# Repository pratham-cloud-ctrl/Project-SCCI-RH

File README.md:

# Project SCCI RH

### A spinal interface concept, from scientific question to inspectable engineering

An entirely digital research and engineering project exploring **invasive spinal
cord–computer interfaces (SCCI)**: record relevant activity, interpret it,
select an individualized intervention, and observe the response.

**Two ambitions:** expert-informed practice that could improve retained motor
learning, and feedback over a selected physiological function.

**[Inspect the build in your browser](https://pratham-cloud-ctrl.github.io/Project-SCCI-RH/)** ·
[Explore the project](docs/explore/README.md) ·
[Read the paper](output/pdf/Project_SCCI_RH_Integrated_Manuscript.pdf) ·
[Download the engineering release](https://github.com/pratham-cloud-ctrl/Project-SCCI-RH/releases/tag/v2.1.1)

**No CAD software needed to inspect:** the browser inspector provides selectable
3D assemblies, all eight populated boards, interactive component/net lookup,
all four copper layers and 80 searchable schematic sheets. The
[download panel](https://pratham-cloud-ctrl.github.io/Project-SCCI-RH/?view=downloads)
also supplies standard **STEP solids**, complete **FreeCAD** files and complete
**KiCad** projects for local inspection and editing.

| Future implanted-interface concept | Full-scale engineering reference |
|:---:|:---:|
|  |  |
| **60 × 58 × 14 mm**, before leads. A proposed miniaturized package. | **600 × 310 × 240 mm**, including feet. Actual board geometry at 1:1 scale. |

## Choose what you want to explore

| | Open the guide | What you can inspect |
|---|---|---|
| **01 · Theory & mechanisms** | [Understand the idea](docs/explore/theory.md) | Both application mechanisms, the assumptions behind them, evidence and mathematical models |
| **02 · CAD & 3D models** | [Explore the mechanical design](docs/explore/cad.md) | Assembled/exploded views, rotatable meshes, editable FreeCAD files, STEP exports and drawings |
| **03 · Electronics & KiCad** | [Browse the eight boards](docs/explore/electronics.md) | Board gallery, circuit roles, schematic PDF, native projects, layouts and component lists |
| **04 · Firmware & software** | [Follow the implemented logic](docs/explore/firmware.md) | Current nRF5340 image, production control code, packet handling and runnable verification |
| **05 · Evidence & reproduction** | [Review the work](docs/explore/reviewer-guide.md) | A short reviewer walkthrough, results, requirements, source records and reproduction commands |

Use the browser inspector for viewing. Links labelled **native source** lead to
engineering files that GitHub may offer only as downloads. Use the complete
packages in the inspector to open them locally; the guides explain the required
software, dependencies and how to preserve the released originals.

## The project in one loop

**Observe → interpret → calibrate → request stimulation → supervise delivery → observe response.**

For motor learning, expert performance informs a task-conditioned reference;
learner-specific calibration determines a reachable intervention during practice.
Later stimulation-OFF probes assess retention separately from assisted performance.
Expert voltage is not replayed as a skill.

For physiological feedback, a function-specific configuration observes a selected
state and requests bounded support. The worked pressure example uses an external
pressure sensor and positive spinal pressor authority. It is a selected pathway,
not a universal body-control mechanism.

## What has been delivered

| Research | Electrical & software | Mechanical |
|---|---|---|
| [29-page illustrated paper](output/pdf/Project_SCCI_RH_Integrated_Manuscript.pdf) | [Eight routed, populated KiCad boards](docs/explore/electronics.md) | [Editable reference and future-interface CAD](docs/explore/cad.md) |
| [18 primary/inspiration references](docs/stage6/evidence-review.md) | [Target-linked nRF5340 firmware](firmware/nrf5340/uart-revision/README.md) | [Six mechanical review sheets](cad/stage5/drawings/SCCI_RH_Stage5_Mechanical_Review.pdf) |
| [Conditional studies and retained negative findings](docs/explore/theory.md) | [Executed production-core digital replay](docs/stage6/integration-verification.md) | [Mapped interfaces, parts and exchange files](docs/explore/cad.md) |

The integrated replay passes **114,426 finite software assertions** and includes
**5,184 modeled motor events** and **1,200 pressure events**. Favorable, neutral
and adverse learning assumptions are retained. These are software/model results;
their implications are explained in the [theory guide](docs/explore/theory.md).

This is a completed **digital concept and engineering reference**. No physical
device execution or original human/animal experiment is claimed. Useful chronic
spinal decoding, retained human benefit and a miniaturized implanted implementation
remain conditional. The current target records in OBSERVE, inhibits neural
acquisition while armed, and has no radio image. The reference boards do not fit
the future can.

## Start, inspect, or contribute

- **First visit:** use the [Explore hub](docs/explore/README.md) or the [five-minute route](docs/explore/reviewer-guide.md#five-minute-overview).
- **Find a file:** use the [repository map](docs/explore/repository-map.md) to distinguish current entry points from historical studies.
- **Check the engineering:** use [verification and reproduction](docs/explore/reviewer-guide.md#reproduce-the-current-engineering).
- **Understand authorship:** read the [contributions](docs/stage6/contributions.md), [defence guide](docs/stage6/defence-guide.md) and [LICENSE](LICENSE).

Pratham Varma conceived and steered Project SCCI RH. AstroSam’s
[Mind-Link](https://github.com/sam-astro/Mind-link) inspired the progression from
future vision to inspectable engineering; SCCI_RH develops its own spinal architecture
and artifacts. Substantial AI assistance is documented in the contribution record.

**Engineering release:** [v2.1.1](https://github.com/pratham-cloud-ctrl/Project-SCCI-RH/releases/tag/v2.1.1).
**Browser inspection and guide refresh:** 21 October 2026. The paper and verified engineering
geometry and circuit behavior are preserved through the recorded name migration. Historical stage records remain available;
use the guides above for the current reading order. The technical inspector
supports engineering review; presentation website and video work remain parked.

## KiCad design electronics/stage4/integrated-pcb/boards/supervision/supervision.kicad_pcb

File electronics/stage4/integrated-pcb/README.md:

# Integrated populated electronics — Project SCCI RH

**Complete within the bounded digital reference scope — 16 October 2026.**
All eight genuinely routed native boards pass DRC with zero violations,
unconnected items, schematic parity issues or ignored checks. The independent
pad/net audit passes 14,273 assertions. The 80-sheet master passes ERC and 9,540
independent electrical-integration assertions.

Start with the [board index and explicit launchers](BOARD_INDEX.md). The
[Stage 4 exit review](../../../docs/stage4/exit-review.md) records what this
package establishes and the remaining physical and biological evidence limits.

The architecture is an eight-board modular digital reference. It preserves the
actual sizes and parts needed by the chosen acquisition, drivers, routing,
independent supervision, supplies and companion interface. The proposed future
implant is explained by the research mechanism; these boards do not demonstrate
implant miniaturization. Use artificial electrical signals and loads.

| Board | Electrical component positions | Initial board outline, mm |
|---|---:|---|
| Monitoring cell | 71 | 120 × 145 |
| Current driver | 156 | 175 × 155 |
| Recording front end | 153 | 155 × 190 |
| Contact router | 155 | 175 × 155 |
| Independent supervision | 479 | 300 × 250 |
| Power | 156 | 175 × 185 |
| Monitoring/companion transport | 60 | 125 × 140 |
| BT40F controller carrier | 68 | 155 × 150 |
| **Total** | **1,298** | Four mounting holes on each board |

There are **1,296 fitted components** and two optional driver capacitors marked
do-not-populate. Those two positions retain their pads and electrical identities;
the fitted STEP assembly and assembly placement file exclude their bodies.

## Open the design

- [Native master schematic](integration/master/SCCI_RH_integrated.kicad_sch):
  80 sheets, 4,781 connected/NC pin identities, all actual circuit symbols.
- [Electrical integration review](../../../docs/stage4/integrated-pcb-design.md),
  [component BOM](integration/populated-bom.csv),
  [258-wire table](../../../docs/stage4/integrated-pcb-wiring.csv), and
  [78 connector / 47 branch-node harness record](integration/harness.json).
- Per-board native designs are in `boards/<board>/`; matching schematics are
  in `integration/boards/<board>/`. Their references and pins use the same
  master electrical graph. The [index](BOARD_INDEX.md) links all native launchers.
- `exports/<board>/` contains populated STEP, native top/bottom/isometric renders,
  copper SVG, source-bound receipts and digital fabrication references.
- [Nominal package geometry](package-models/README.md) identifies the eight
  missing package patterns represented by actual FreeCAD solids and STEP.
- [Carrier-specific firmware](firmware-profile/build-receipt.json) uses the
  compiled application and a manufacturer-supported 11 pF HFXO setting.
  Earlier firmware artifacts remain preserved.

## Power and implemented domain

[The new additive budget](power-overlay.json) preserves previous load reserves
and adds the actual controller: HOST_3V3 is allocated 160 mA, including 41 bias
resistors. Calculated active consumption is **3.154 W** and conditional runtime
is **4.880 h**, using the existing battery/efficiency assumptions. These are not
physical measurements. The earlier compact implanted thermal failure remains.

The target firmware implements nominal 100 µs raw acquisition opportunities and
1 ms recording frames with explicit gaps and validity, rather than the earlier
450k aggregate / 4k neural proposal. Direct independent guards retain shutdown
authority; serialized health is an additional observation path. Expert-informed
retained learning and function-specific physiological regulation remain
conditional biological mechanisms, not measured outcomes of this board set.

## Reproduce finite checks

From the repository root:

```text
python electronics/stage4/controller-carrier/verify_controller_carrier.py
python electronics/stage4/integrated-pcb/integration/verify_integration.py
python electronics/stage4/integrated-pcb/power_overlay.py
python electronics/stage4/integrated-pcb/verify_power.py
```

Saved native ERC, PCB routing/DRC and independent integration checks pass.
There are 21,039 trace segments and 2,335 vias. Manufacturing, analog settling,
timing/WCET, actual current accuracy, noise, EMI, leakage, chronic packaging and
biological efficacy require evidence beyond this digital package. Stage 5
develops the mechanical assembly and interfaces; Stage 6 joins the paper and
verified private repository release. Video and website work remain parked.

Initial DSN/SES and finite repair journals record construction history. The saved
final boards and current hash-bound native checks are authoritative; do not
reimport an initial SES over a finished board. See the [layout review](../../../docs/stage4/pcb-layout-review.md)
for stackup, route limits, the corrected TPS3431 land pattern and the five
controller LGA lands that require a filled/capped via process.

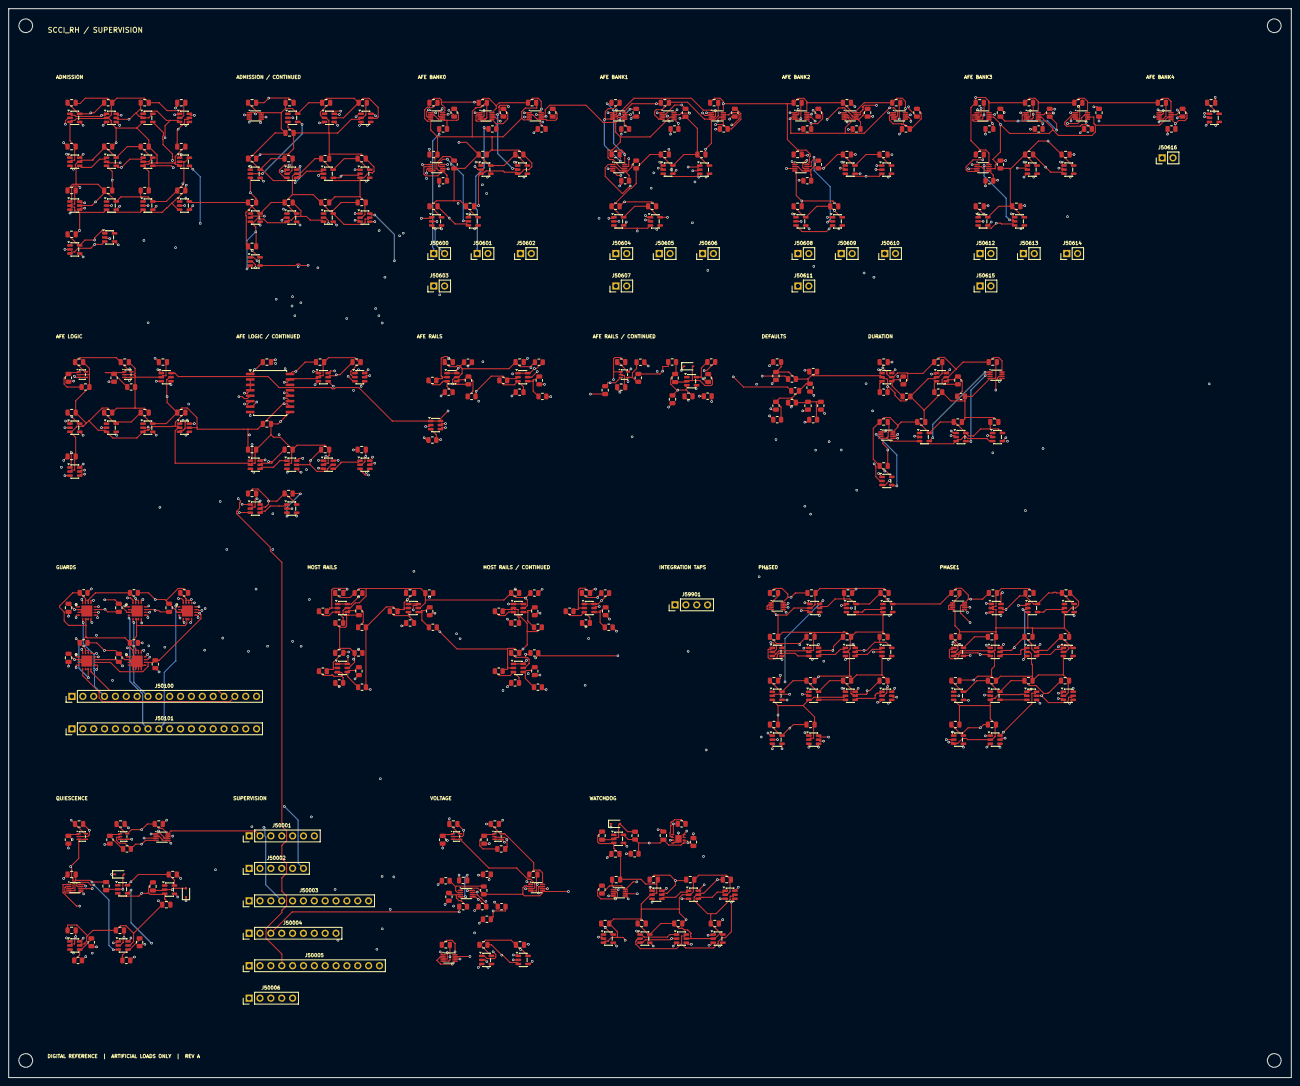
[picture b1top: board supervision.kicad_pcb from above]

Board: 4 copper layers, 300.0 x 250.0 mm, 483 parts (0 on the bottom side), 320 nets.

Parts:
C50100, C50101, C50102, C50103, C50104: 100n X7R 50V; C_0805_2012Metric
C50200, C50201, C50202, C50203, C50204, C50205, C50206, C50207, C50208, C50220, C50251, C50261, C50300, C50301, C50400, C50401, C50410, C50411, C50430, C50431, C50500, C50501, C50502, C50510, C50520, C50600, C50601, C50602, C50603, C50604, C50605, C50606, C50607, C50608, C50609, C50610, C50611, C50612, C50613, C50614, C50615, C50616, C50700, C50701, C50710, C50711, C50800, C50801, C50810, C50811, C50900, C50910, C50911, C51000, C51001, C51002, C51003, C51004, C51005, C51006, C51007, C51008, C51009, C51010, C51011, C51012, C51013, C51014, C51015, C51016, C51017, C51018, C51019, C51020, C51021, C51022, C51023, C51024, C51025, C51026, C51027, C51028, C51029, C51030, C51031, C51032, C51033, C51034, C51035, C51036, C51037, C51038, C51039, C51040, C51041, C51042, C51043, C51044, C51045, C51046, C51047, C51048, C51049, C51050, C51051, C51052, C51053, C51054, C51055, C51056, C51057, C51058, C51059, C51060, C51061, C51062, C51063, C51064, C51065, C51066, C51067, C51068, C51069, C51070, C51071, C51072, C51073, C51074, C51075, C51076, C51077, C51078, C51079, C51080, C51081, C51082, C51083, C51084, C51085, C51086, C51087, C51088, C51089, C51090, C51091, C51092, C51093, C51094, C51095, C51096, C51097: 100n X7R 16V; C_0805_2012Metric
C50250, C50260: 47n X7R 10%; C_0805_2012Metric
C50420, C50421: 10n C0G 5%; C_0805_2012Metric
D50250, D50260, D50410, D50411: BAT54WS-7-F; D_SOD-323
H1, H2, H3, H4: MountingHole_3.2mm_M3
J50001: EXTERNAL SUPERVISOR AND HOST RAILS; PinHeader_1x07_P2.54mm_Vertical
J50002: FLOATING AFE RAILS AND OBSERVED CONTROLS; PinHeader_1x06_P2.54mm_Vertical
J50003: RAW CONTROL / STATUS; PinHeader_1x12_P2.54mm_Vertical
J50004: EXISTING MONITOR OBSERVATIONS; PinHeader_1x09_P2.54mm_Vertical
J50005: EXPORTED NATIVE HEALTH / PERMISSION; PinHeader_1x13_P2.54mm_Vertical
J50006: DRIVER INTERNAL DIFFERENTIAL VOLTAGES; PinHeader_1x05_P2.54mm_Vertical
J50100: CANONICAL ROUTER J7 / BEFORE GUARDS; PinHeader_1x18_P2.54mm_Vertical
J50101: BODY-FACING ARTIFICIAL LOAD CONTACTS; PinHeader_1x18_P2.54mm_Vertical
J50600: REC00 ACTUAL RHD-SIDE TAP; PinHeader_1x02_P2.54mm_Vertical
J50601: REC01 ACTUAL RHD-SIDE TAP; PinHeader_1x02_P2.54mm_Vertical
J50602: REC02 ACTUAL RHD-SIDE TAP; PinHeader_1x02_P2.54mm_Vertical
J50603: REC03 ACTUAL RHD-SIDE TAP; PinHeader_1x02_P2.54mm_Vertical
J50604: REC04 ACTUAL RHD-SIDE TAP; PinHeader_1x02_P2.54mm_Vertical
J50605: REC05 ACTUAL RHD-SIDE TAP; PinHeader_1x02_P2.54mm_Vertical
J50606: REC06 ACTUAL RHD-SIDE TAP; PinHeader_1x02_P2.54mm_Vertical
J50607: REC07 ACTUAL RHD-SIDE TAP; PinHeader_1x02_P2.54mm_Vertical
J50608: REC08 ACTUAL RHD-SIDE TAP; PinHeader_1x02_P2.54mm_Vertical
J50609: REC09 ACTUAL RHD-SIDE TAP; PinHeader_1x02_P2.54mm_Vertical
J50610: REC10 ACTUAL RHD-SIDE TAP; PinHeader_1x02_P2.54mm_Vertical
J50611: REC11 ACTUAL RHD-SIDE TAP; PinHeader_1x02_P2.54mm_Vertical
J50612: REC12 ACTUAL RHD-SIDE TAP; PinHeader_1x02_P2.54mm_Vertical
J50613: REC13 ACTUAL RHD-SIDE TAP; PinHeader_1x02_P2.54mm_Vertical
J50614: REC14 ACTUAL RHD-SIDE TAP; PinHeader_1x02_P2.54mm_Vertical
J50615: REC15 ACTUAL RHD-SIDE TAP; PinHeader_1x02_P2.54mm_Vertical
J50616: REF ACTUAL RHD-SIDE TAP; PinHeader_1x02_P2.54mm_Vertical
J59901: HOST TAP HARNESS; PinHeader_1x04_P2.54mm_Vertical
R50100, R50101, R50102, R50103, R50104: 22k; R_0805_2012Metric
R50110: 1k; R_0805_2012Metric
R50250, R50260: 100k 1%; R_0805_2012Metric
R50251, R50261, R50420, R50421: 100R; R_0805_2012Metric
R50300, R50301, R50302, R50950, R50951, R50952, R50953, R50954, R50955, R50956, R50957, R50958, R50959, R50960, R50961, R52004, R52014, R52024, R52034, R52044, R52054, R52064, R52074, R52084: 10k; R_0805_2012Metric
R50400, R50402: 203.8k 0.1%; R_0805_2012Metric
R50401: 2k 0.1%; R_0805_2012Metric
R50410, R50411: 3.3k 1%; R_0805_2012Metric
R50500, R50502: 232k 0.1%; R_0805_2012Metric
R50501: 536k 0.1%; R_0805_2012Metric
R50510, R50512, R50520, R50522, R56001, R56011, R56021, R56031, R56041, R56051, R56061, R56071, R56081, R56091, R56101, R56111, R56121, R56131, R56141, R56151, R56161: 1M 0.1%; R_0805_2012Metric
R50511, R50513, R50521, R50523: 49.9k 0.1%; R_0805_2012Metric
R50700: 9.50k 0.1%; R_0805_2012Metric
R50701, R50703, R52200: 100k 0.1%; R_0805_2012Metric
R50702: 10.5k 0.1%; R_0805_2012Metric
R52000, R52020: 67500R 0.1%; R_0805_2012Metric
R52001, R52003, R52011, R52013, R52021, R52023, R52031, R52033, R52041, R52043, R52051, R52053, R52061, R52063, R52071, R52073, R52081, R52083, R52201: 10k 0.1%; R_0805_2012Metric
R52002, R52022: 77500R 0.1%; R_0805_2012Metric
R52010, R52030: 108750R 0.1%; R_0805_2012Metric
R52012, R52032: 121250R 0.1%; R_0805_2012Metric
R52040: 327500R 0.1%; R_0805_2012Metric
R52042: 402500R 0.1%; R_0805_2012Metric
R52050: 560000R 0.1%; R_0805_2012Metric
R52052: 620000R 0.1%; R_0805_2012Metric
R52060: 73500R 0.1%; R_0805_2012Metric
R52062: 78500R 0.1%; R_0805_2012Metric
R52070: 120000R 0.1%; R_0805_2012Metric
R52072: 125500R 0.1%; R_0805_2012Metric
R52080: 1875R 0.1%; R_0805_2012Metric
R52082: 3750R 0.1%; R_0805_2012Metric
R56000, R56010, R56020, R56030, R56040, R56050, R56060, R56070, R56080, R56090, R56100, R56110, R56120, R56130, R56140, R56150, R56160: 10M 0.1%; R_0805_2012Metric
R58000, R58010: 195.4k 0.1%; R_0805_2012Metric
R58001, R58011: 976k 0.1%; R_0805_2012Metric
R58002, R58012: 182k 0.1%; R_0805_2012Metric
U50100, U50101, U50102, U50103, U50104: TMUX7412FRRPR; Texas_RRP0016A_WQFN16_4x4_P0.65_EP2.6
U50200, U50201, U50202, U50203, U50204, U50205, U50206, U50207, U50208: TPS3700DDCR; SOT-23-6
U50220, U50400, U50401, U50500, U50501, U50700, U50701: OPA391DCKR; SOT-353_SC-70-5
U50250, U50260, U50420, U50421: SN74LVC1G17DBVR; SOT-23-5
U50300: TPS3431SDRBR; Texas_DRB0008A_VSON8_3x3_P0.65_EP1.5x1.75
U50301, U50810, U50811, U50900, U50910, U50911: SN74LVC1G74DCUR; VSSOP-8_2.3x2mm_P0.5mm
U50410, U50411, U50510, U50520, U50600, U50601, U50602, U50603, U50604, U50605, U50606, U50607, U50608, U50609, U50610, U50611, U50612, U50613, U50614, U50615, U50616: TLV3202DGKR; VSSOP-8_2.3x2mm_P0.5mm
U50502: OPA2192IDGKR; VSSOP-8_2.3x2mm_P0.5mm
U50710: ISO6742FDWR; SOIC-16W_7.5x10.3mm_P1.27mm
U50800, U50801: LTC6993HS6-1#TRPBF; TSOT-23-6
U51000, U51001, U51002, U51003, U51007, U51009, U51010, U51032, U51033, U51034, U51035, U51036, U51037, U51038, U51039, U51040, U51047, U51049, U51050, U51054, U51061, U51062, U51064, U51070, U51071, U51075, U51076, U51080, U51081, U51083, U51084, U51088, U51089, U51093, U51094, U51096: SN74LVC1G11DBVR; SOT-23-6
U51004, U51006, U51008, U51011, U51012, U51013, U51014, U51015, U51016, U51017, U51018, U51019, U51020, U51021, U51022, U51023, U51024, U51025, U51026, U51027, U51028, U51029, U51041, U51046, U51048, U51051, U51052, U51053, U51063, U51065, U51066, U51072, U51074, U51077, U51082, U51085, U51087, U51090, U51095: SN74LVC1G08DBVR; SOT-23-5
U51005, U51030, U51031, U51042, U51044, U51055, U51056, U51057, U51058, U51059, U51060, U51067, U51068, U51069, U51073, U51078, U51079, U51086, U51091, U51092: SN74LVC1G04DBVR; SOT-23-5
U51043, U51045, U51097: SN74LVC1G32DBVR; SOT-23-5

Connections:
SYS_0bc4e447__AFE_CONNECT: J50002.5, U51030.2
SYS_0d1e7c21__CH0_RETURN_LOAD: J50100.17, U50104.16
SYS_1dc2a435__AFE_IN08_P: J50608.1, R56080.1
SYS_2d0e5b2e__CH0_QUIESCENT_OK: J50005.5, U50420.4, U51064.3, U51075.6
SYS_3ced048f__CH1_RETURN_LOAD: J50100.18, U50104.13
SYS_3fdd5066__AFE_P5: C50600.1, C50601.1, C50602.1, C50603.1, C50604.1, C50605.1, C50606.1, C50607.1, C50608.1, C50609.1, C50610.1, C50611.1, C50612.1, C50613.1, C50614.1, C50615.1, C50616.1, C50700.1, C50701.1, J50002.2, R52070.1, R52072.1, U50600.8, U50601.8, U50602.8, U50603.8, U50604.8, U50605.8, U50606.8, U50607.8, U50608.8, U50609.8, U50610.8, U50611.8, U50612.8, U50613.8, U50614.8, U50615.8, U50616.8, U50700.5, U50701.5
SYS_4eb6b999__AFE_ACQUIRE: J50002.6, U51031.2
SYS_4f7d5988__AFE_IN14_P: J50614.1, R56140.1
SYS_4f66f129__MON_VREF: J50004.4, R50400.1, R50500.1
SYS_4fabccc5__AFE_IN12_P: J50612.1, R56120.1
SYS_6a132103__CH1_RUN: J50003.7, R50957.1, U51059.2, U51095.2
SYS_6d4bb3d1__STIM11_CONTACT: J50100.12, U50102.5
SYS_7db86ec0__PHASE_REARM0: J50003.10, R50952.1, U51075.1
SYS_7e367734__AFE_IN04_P: J50604.1, R56040.1
SYS_8b50701c__STIM01_CONTACT: J50100.2, U50100.13
SYS_8c3f25bb__AFE_IN02_P: J50602.1, R56020.1
SYS_20eba8c2__CH1_QUIESCENT_OK: J50005.6, U50421.4, U51064.6, U51088.6
SYS_32c4c1cc__AFE_IN13_P: J50613.1, R56130.1
SYS_32f1b236__STIM12_CONTACT: J50100.13, U50103.16
SYS_36b8c84f__STIM02_CONTACT: J50100.3, U50100.8
SYS_37cfe02a__MON_VMID: J50004.3, R50511.1, R50521.1
SYS_40eeaa0c__CH1_VPAIR: J59901.2, R50523.1, U50502.7, U50520.2, U50520.5
SYS_46e29157__PHASE_REARM1: J50003.11, R50953.1, U51088.1
SYS_46ea5f03__CH0_REQUEST: J50003.4, R50954.1, U50800.1, U51043.2, U51055.2, U51081.3
SYS_56ebc071__CH0_MON_PERMIT: J50004.5, R50960.1, U51009.6, U51054.3
SYS_65aafbb6__AFE_3V3: C50206.1, C50207.1, C50208.1, C50220.1, C50261.1, C50711.1, C51003.1, C51004.1, C51013.1, C51014.1, C51015.1, C51016.1, C51017.1, C51018.1, C51019.1, C51020.1, C51021.1, C51022.1, C51023.1, C51024.1, C51025.1, C51026.1, C51027.1, C51028.1, C51029.1, C51030.1, C51031.1, C51032.1, C51033.1, C51034.1, C51035.1, C51036.1, C51037.1, C51038.1, C51039.1, C51040.1, C51041.1, J50002.1, R50260.1, R50261.2, R50700.1, R50702.1, R52060.1, R52062.1, R52064.1, R52074.1, R52084.1, R56001.1, R56011.1, R56021.1, R56031.1, R56041.1, R56051.1, R56061.1, R56071.1, R56081.1, R56091.1, R56101.1, R56111.1, R56121.1, R56131.1, R56141.1, R56151.1, R56161.1, U50206.5, U50207.5, U50208.5, U50220.5, U50260.5, U50710.10, U50710.16, U51003.5, U51004.5, U51013.5, U51014.5, U51015.5, U51016.5, U51017.5, U51018.5, U51019.5, U51020.5, U51021.5, U51022.5, U51023.5, U51024.5, U51025.5, U51026.5, U51027.5, U51028.5, U51029.5, U51030.5, U51031.5, U51032.5, U51033.5, U51034.5, U51035.5, U51036.5, U51037.5, U51038.5, U51039.5, U51040.5, U51041.5
SYS_66aba95b__SUP_5: C50400.1, C50401.1, C50410.1, C50411.1, C50500.1, C50501.1, C50502.1, C50510.1, C50520.1, J50001.2, R52010.1, R52012.1, U50400.5, U50401.5, U50410.8, U50411.8, U50500.5, U50501.5, U50502.8, U50510.8, U50520.8
SYS_74b9e55a__STIM10_CONTACT: J50100.11, U50102.8
SYS_77c24b0d__GLOBAL_GUARD_EN: J50005.12, R50100.1, R50101.1, R50102.1, R50103.1, R50104.1, U50100.6, U50100.7, U50100.14, U50100.15, U50101.6, U50101.7, U50101.14, U50101.15, U50102.6, U50102.7, U50102.14, U50102.15, U50103.6, U50103.7, U50103.14, U50103.15, U50104.14, U50104.15, U51097.4
SYS_84f28705__CH1_ROUTE_LOCKED: J50003.9, R50959.1, U51084.6
SYS_86b728f8__AFE_REF: J50616.1, R56160.1
SYS_88c50083__SUP_ARMED: J50005.9, U50900.5, U51071.3, U51083.3, U51084.3, U51096.3
SYS_96d7c46a__AFE_IN10_P: J50610.1, R56100.1
SYS_126bf237__STIM14_CONTACT: J50100.15, U50103.8
SYS_223a43dd__STIM03_CONTACT: J50100.4, U50100.5
SYS_401be33b__CH1_A_ROUTER: J50006.3, R50520.1
SYS_502efdd4__CH1_I_MON: J50004.2, U50411.2, U50411.5
SYS_695f3a7c__CH0_RUN: J50003.6, R50956.1, U51056.2, U51082.2
SYS_917b1360__CH0_A_ROUTER: J50006.1, R50510.1
SYS_3232ae4c__AFE_IN01_P: J50601.1, R56010.1
SYS_8359fceb__CH1_EXT_SUP_OK: J50005.8, U51096.4
SYS_15689dc4__VH_24: C50100.1, C50101.1, C50102.1, C50103.1, C50104.1, J50001.6, R52050.1, R52052.1, U50100.11, U50101.11, U50102.11, U50103.11, U50104.11
SYS_53213f89__AFE_IN15_P: J50615.1, R56150.1
SYS_56562df4__GND: C50100.2, C50101.2, C50102.2, C50103.2, C50104.2, C50200.2, C50201.2, C50202.2, C50203.2, C50204.2, C50205.2, C50250.2, C50251.2, C50300.2, C50301.2, C50400.2, C50401.2, C50410.2, C50411.2, C50420.2, C50421.2, C50430.2, C50431.2, C50500.2, C50501.2, C50502.2, C50510.2, C50520.2, C50710.2, C50800.2, C50801.2, C50810.2, C50811.2, C50900.2, C50910.2, C50911.2, C51000.2, C51001.2, C51002.2, C51005.2, C51006.2, C51007.2, C51008.2, C51009.2, C51010.2, C51011.2, C51012.2, C51042.2, C51043.2, C51044.2, C51045.2, C51046.2, C51047.2, C51048.2, C51049.2, C51050.2, C51051.2, C51052.2, C51053.2, C51054.2, C51055.2, C51056.2, C51057.2, C51058.2, C51059.2, C51060.2, C51061.2, C51062.2, C51063.2, C51064.2, C51065.2, C51066.2, C51067.2, C51068.2, C51069.2, C51070.2, C51071.2, C51072.2, C51073.2, C51074.2, C51075.2, C51076.2, C51077.2, C51078.2, C51079.2, C51080.2, C51081.2, C51082.2, C51083.2, C51084.2, C51085.2, C51086.2, C51087.2, C51088.2, C51089.2, C51090.2, C51091.2, C51092.2, C51093.2, C51094.2, C51095.2, C51096.2, C51097.2, J50001.7, J50003.12, J50004.9, J50005.13, J50006.5, J59901.4, R50100.2, R50101.2, R50102.2, R50103.2, R50104.2, R50302.2, R50402.2, R50502.2, R50950.2, R50951.2, R50952.2, R50953.2, R50954.2, R50955.2, R50956.2, R50957.2, R50958.2, R50959.2, R50960.2, R50961.2, R52001.2, R52003.2, R52011.2, R52013.2, R52021.2, R52023.2, R52031.2, R52033.2, R52041.2, R52043.2, R52051.2, R52053.2, R58000.2, R58002.2, R58010.2, R58012.2, U50100.2, U50100.3, U50100.17, U50101.2, U50101.3, U50101.17, U50102.2, U50102.3, U50102.17, U50103.2, U50103.3, U50103.17, U50104.2, U50104.3, U50104.4, U50104.5, U50104.6, U50104.7, U50104.8, U50104.9, U50104.17, U50200.2, U50201.2, U50202.2, U50203.2, U50204.2, U50205.2, U50250.3, U50300.4, U50300.9, U50301.4, U50400.2, U50401.2, U50410.4, U50411.4, U50420.3, U50421.3, U50500.2, U50501.2, U50502.4, U50510.4, U50520.4, U50710.2, U50710.3, U50710.4, U50710.8, U50800.2, U50801.2, U50810.4, U50811.4, U50900.4, U50910.1, U50910.2, U50910.4, U50911.1, U50911.2, U50911.4, U51000.2, U51001.2, U51002.2, U51005.3, U51006.3, U51007.2, U51008.3, U51009.2, U51010.2, U51011.3, U51012.3, U51042.3, U51043.3, U51044.3, U51045.3, U51046.3, U51047.2, U51048.3, U51049.2, U51050.2, U51051.3, U51052.3, U51053.3, U51054.2, U51055.3, U51056.3, U51057.3, U51058.3, U51059.3, U51060.3, U51061.2, U51062.2, U51063.3, U51064.2, U51065.3, U51066.3, U51067.3, U51068.3, U51069.3, U51070.2, U51071.2, U51072.3, U51073.3, U51074.3, U51075.2, U51076.2, U51077.3, U51078.3, U51079.3, U51080.2, U51081.2, U51082.3, U51083.2, U51084.2, U51085.3, U51086.3, U51087.3, U51088.2, U51089.2, U51090.3, U51091.3, U51092.3, U51093.2, U51094.2, U51095.3, U51096.2, U51097.3
SYS_59100ef9__AFE_IN05_P: J50605.1, R56050.1
SYS_80673a9e__STIM08_CONTACT: J50100.9, U50102.16
SYS_82867ca5__STIM00_CONTACT: J50100.1, U50100.16
SYS_98321c7b__AFE_ISOLATED_READY: J50005.4, U51048.4
SYS_325713b8__AFE_IN07_P: J50607.1, R56070.1
SYS_344482b2__STIM13_CONTACT: J50100.14, U50103.13
SYS_380216f6__AFE_IN06_P: J50606.1, R56060.1
SYS_1954027d__CH0_ROUTE_LOCKED: J50003.8, R50958.1, U51071.6
SYS_05097029__AFE_IN00_P: J50600.1, R56000.1
SYS_08572049__HOST_3V3: J50001.3, R52020.1, R52022.1
SYS_82531809__FAULT_RESET: J50003.2, R50951.1, U51066.1
SYS_93547907__RAILS_QUALIFIED: J50005.2, U51046.4
SYS_a83d484c__WATCHDOG_OK: J50005.3, U51008.4
SYS_aa321af6__CH1_MON_PERMIT: J50004.6, R50961.1, U51010.6, U51054.6
SYS_ab932142__SUP_3V3: C50200.1, C50201.1, C50202.1, C50203.1, C50204.1, C50205.1, C50251.1, C50300.1, C50301.1, C50430.1, C50431.1, C50710.1, C50800.1, C50801.1, C50810.1, C50811.1, C50900.1, C50910.1, C50911.1, C51000.1, C51001.1, C51002.1, C51005.1, C51006.1, C51007.1, C51008.1, C51009.1, C51010.1, C51011.1, C51012.1, C51042.1, C51043.1, C51044.1, C51045.1, C51046.1, C51047.1, C51048.1, C51049.1, C51050.1, C51051.1, C51052.1, C51053.1, C51054.1, C51055.1, C51056.1, C51057.1, C51058.1, C51059.1, C51060.1, C51061.1, C51062.1, C51063.1, C51064.1, C51065.1, C51066.1, C51067.1, C51068.1, C51069.1, C51070.1, C51071.1, C51072.1, C51073.1, C51074.1, C51075.1, C51076.1, C51077.1, C51078.1, C51079.1, C51080.1, C51081.1, C51082.1, C51083.1, C51084.1, C51085.1, C51086.1, C51087.1, C51088.1, C51089.1, C51090.1, C51091.1, C51092.1, C51093.1, C51094.1, C51095.1, C51096.1, C51097.1, J50001.1, R50110.1, R50250.1, R50251.2, R50300.1, R50301.1, R52000.1, R52002.1, R52004.1, R52014.1, R52024.1, R52034.1, R52044.1, R52054.1, R58001.1, R58011.1, U50200.5, U50201.5, U50202.5, U50203.5, U50204.5, U50205.5, U50250.5, U50300.1, U50300.5, U50301.7, U50301.8, U50420.5, U50421.5, U50710.1, U50710.7, U50800.5, U50801.5, U50810.7, U50810.8, U50811.7, U50811.8, U50900.7, U50900.8, U50910.8, U50911.8, U51000.5, U51001.5, U51002.5, U51005.5, U51006.5, U51007.5, U51008.2, U51008.5, U51009.5, U51010.5, U51011.5, U51012.5, U51042.5, U51043.5, U51044.5, U51045.5, U51046.5, U51047.5, U51048.2, U51048.5, U51049.5, U51050.5, U51051.5, U51052.2, U51052.5, U51053.2, U51053.5, U51054.5, U51055.5, U51056.5, U51057.5, U51058.5, U51059.5, U51060.5, U51061.5, U51062.5, U51063.5, U51064.5, U51065.5, U51066.5, U51067.5, U51068.5, U51069.5, U51070.5, U51071.5, U51072.5, U51073.5, U51074.5, U51075.5, U51076.5, U51077.5, U51078.5, U51079.5, U51080.5, U51081.5, U51082.5, U51083.5, U51084.5, U51085.5, U51086.5, U51087.5, U51088.5, U51089.5, U51090.5, U51091.5, U51092.5, U51093.5, U51094.5, U51095.5, U51096.5, U51097.5
SYS_b6a4cd67__AFE_IN11_P: J50611.1, R56110.1
SYS_b675ff0d__STIM06_CONTACT: J50100.7, U50101.8
SYS_baff84b5__CH0_VPAIR: J59901.1, R50513.1, U50502.1, U50510.2, U50510.5
SYS_bb444a6e__SUP_REARM: J50003.1, R50950.1, U50900.1
SYS_c73180be__CH1_B_BR: J50006.4, R50522.1
SYS_ce166826__HOST_5: J50001.4, R52030.1, R52032.1
SYS_cf17d7c4__STIM07_CONTACT: J50100.8, U50101.5
SYS_d3eac10b__CH0_EXT_SUP_OK: J50004.7, U51052.4
SYS_d73cd2ee__AFE_N5: J50002.3, R52200.1
SYS_dcbe1273__STIM04_CONTACT: J50100.5, U50101.16
SYS_dd388269__CH1_REQUEST: J50003.5, R50955.1, U50801.1, U51045.2, U51058.2, U51094.3
SYS_de0a854a__CH1_EXT_SUP_OK: J50004.8, U51053.4
SYS_e3faaec0__WDI: J50003.3, R50302.1, U50300.6, U51005.2
SYS_e26747fb__CH0_EXT_SUP_OK: J50005.7, U51083.4
SYS_eb2c0acf__STIM09_CONTACT: J50100.10, U50102.13
SYS_ee59c76b__PWR_FAULT_N: J59901.3, R50110.2, U50100.10, U50101.10, U50102.10, U50103.10, U50104.10, U51050.3
SYS_ee476f53__CH0_B_BR: J50006.2, R50512.1
SYS_ee730a89__AFE_IN09_P: J50609.1, R56090.1
SYS_f00e6304__STIM15_CONTACT: J50100.16, U50103.5
SYS_f8e43b73__CH0_I_MON: J50004.1, U50410.2, U50410.5
SYS_f208be39__AFE_IN03_P: J50603.1, R56030.1
SYS_fa6c9e06__STIM05_CONTACT: J50100.6, U50101.13
SYS_fb2237f8__VA_15: J50001.5, R52040.1, R52042.1
SYS_fca1c340__AFEAGND: C50206.2, C50207.2, C50208.2, C50220.2, C50260.2, C50261.2, C50600.2, C50601.2, C50602.2, C50603.2, C50604.2, C50605.2, C50606.2, C50607.2, C50608.2, C50609.2, C50610.2, C50611.2, C50612.2, C50613.2, C50614.2, C50615.2, C50616.2, C50700.2, C50701.2, C50711.2, C51003.2, C51004.2, C51013.2, C51014.2, C51015.2, C51016.2, C51017.2, C51018.2, C51019.2, C51020.2, C51021.2, C51022.2, C51023.2, C51024.2, C51025.2, C51026.2, C51027.2, C51028.2, C51029.2, C51030.2, C51031.2, C51032.2, C51033.2, C51034.2, C51035.2, C51036.2, C51037.2, C51038.2, C51039.2, C51040.2, C51041.2, J50002.4, J50600.2, J50601.2, J50602.2, J50603.2, J50604.2, J50605.2, J50606.2, J50607.2, J50608.2, J50609.2, J50610.2, J50611.2, J50612.2, J50613.2, J50614.2, J50615.2, J50616.2, R50701.2, R50703.2, R52061.2, R52063.2, R52071.2, R52073.2, R52081.2, R52083.2, U50206.2, U50207.2, U50208.2, U50220.1, U50220.2, U50260.3, U50600.4, U50601.4, U50602.4, U50603.4, U50604.4, U50605.4, U50606.4, U50607.4, U50608.4, U50609.4, U50610.4, U50611.4, U50612.4, U50613.4, U50614.4, U50615.4, U50616.4, U50700.2, U50701.2, U50710.9, U50710.15, U51003.2, U51004.3, U51013.3, U51014.3, U51015.3, U51016.3, U51017.3, U51018.3, U51019.3, U51020.3, U51021.3, U51022.3, U51023.3, U51024.3, U51025.3, U51026.3, U51027.3, U51028.3, U51029.3, U51030.3, U51031.3, U51032.2, U51033.2, U51034.2, U51035.2, U51036.2, U51037.2, U51038.2, U51039.2, U51040.2, U51041.3
SYS_ff7fdc58__RESET_READY: J50005.1, U51047.4
supervision__A3_OV: R52062.2, R52063.1, U50206.4
supervision__A3_RAIL_OK: R52064.2, U50206.1, U50206.6, U51003.1
supervision__A3_UV: R52060.2, R52061.1, U50206.3
supervision__AFE_ACQUIRE_LOW: U51031.4, U51040.6
supervision__AFE_ALL_DC_OK: U51039.4, U51040.1
supervision__AFE_ALL_DC_OK_G5: U51038.4, U51039.1
supervision__AFE_ALL_DC_OK_G7: U51037.4, U51038.1
supervision__AFE_ALL_DC_OK_G9: U51036.4, U51037.1
supervision__AFE_ALL_DC_OK_G11: U51035.4, U51036.1
supervision__AFE_ALL_DC_OK_G13: U51034.4, U51035.1
supervision__AFE_ALL_DC_OK_G15: U51033.4, U51034.1
supervision__AFE_ALL_DC_OK_G17: U51032.4, U51033.1
supervision__AFE_BLANK_LOCAL_OK: U50710.11, U51041.4
supervision__AFE_BLANK_LOCAL_OK_G4: U51040.4, U51041.1
supervision__AFE_BLANK_OBS_OK: U50710.6, U51048.1, U51049.3
supervision__AFE_CONNECT_LOW: U51030.4, U51040.3
supervision__AFE_DIS: D50260.1, R50261.1
supervision__AFE_NINV: R52200.2, R52201.2, U50220.3
supervision__AFE_NMAG: R52080.1, R52082.1, R52201.1, U50220.4
supervision__AFE_RAIL_LOCAL_OK: U50710.12, U51004.4, U51041.2
supervision__AFE_RAIL_LOCAL_OK_G4: U51003.4, U51004.1
supervision__AFE_RAIL_OBS_OK: U50710.5, U51046.2, U51047.3
supervision__AFE_RC: C50260.1, D50260.2, R50260.2, U50260.2
supervision__AFE_STARTUP_OK: U50260.4, U51004.2
supervision__AFE_WIN_HI: U50600.3, U50601.3, U50602.3, U50603.3, U50604.3, U50605.3, U50606.3, U50607.3, U50608.3, U50609.3, U50610.3, U50611.3, U50612.3, U50613.3, U50614.3, U50615.3, U50616.3, U50700.3, U50700.4
supervision__AFE_WIN_HI_DIV: R50700.2, R50701.1, U50700.1
supervision__AFE_WIN_LO: U50600.6, U50601.6, U50602.6, U50603.6, U50604.6, U50605.6, U50606.6, U50607.6, U50608.6, U50609.6, U50610.6, U50611.6, U50612.6, U50613.6, U50614.6, U50615.6, U50616.6, U50701.3, U50701.4
supervision__AFE_WIN_LO_DIV: R50702.2, R50703.1, U50701.1
supervision__AN_OV: R52082.2, R52083.1, U50208.4
supervision__AN_RAIL_OK: R52084.2, U50208.1, U50208.6, U51003.6
supervision__AN_UV: R52080.2, R52081.1, U50208.3
supervision__AP_OV: R52072.2, R52073.1, U50207.4
supervision__AP_RAIL_OK: R52074.2, U50207.1, U50207.6, U51003.3
supervision__AP_UV: R52070.2, R52071.1, U50207.3
supervision__ARM_CLR_N: U50900.6, U51070.4
supervision__BODY_RETURN0: J50101.17, U50104.1
supervision__BODY_RETURN1: J50101.18, U50104.12
supervision__BODY_STIM00: J50101.1, U50100.1
supervision__BODY_STIM01: J50101.2, U50100.12
supervision__BODY_STIM02: J50101.3, U50100.9
supervision__BODY_STIM03: J50101.4, U50100.4
supervision__BODY_STIM04: J50101.5, U50101.1
supervision__BODY_STIM05: J50101.6, U50101.12
supervision__BODY_STIM06: J50101.7, U50101.9
supervision__BODY_STIM07: J50101.8, U50101.4
supervision__BODY_STIM08: J50101.9, U50102.1
supervision__BODY_STIM09: J50101.10, U50102.12
supervision__BODY_STIM10: J50101.11, U50102.9
supervision__BODY_STIM11: J50101.12, U50102.4
supervision__BODY_STIM12: J50101.13, U50103.1
supervision__BODY_STIM13: J50101.14, U50103.12
supervision__BODY_STIM14: J50101.15, U50103.9
supervision__BODY_STIM15: J50101.16, U50103.4
supervision__CH0_ALLOW: J50005.10, U51082.4, U51097.1
supervision__CH0_ALLOW_G4: U51081.4, U51082.1
supervision__CH0_ALLOW_G6: U51080.4, U51081.1
supervision__CH0_BLOCK: U50910.5, U51079.2
supervision__CH0_BLOCK_CLR_N: U50910.6, U51078.4
supervision__CH0_BLOCK_PRE_N: U50910.7, U51074.4
supervision__CH0_DIFF_N: R50512.2, R50513.2, U50502.2
supervision__CH0_DIFF_P: R50510.2, R50511.2, U50502.3
supervision__CH0_ENDED: U51072.4, U51073.2
supervision__CH0_NO_BLOCK: U51079.4, U51080.3
supervision__CH0_NO_TIMEOUT: U51068.4, U51070.3, U51080.6, U51083.6
supervision__CH0_PAIR_HI_OK: U50510.1, U51011.1
supervision__CH0_PAIR_LO_OK: U50510.7, U51011.2
supervision__CH0_PAIR_OK: U51011.4, U51050.6
supervision__CH0_PHASE_HEALTH: U51071.4, U51074.1, U51075.3, U51080.1
supervision__CH0_PHASE_REARM_SAFE: U51077.4, U51078.2
supervision__CH0_PHASE_REARM_SAFE_G4: U51076.4, U51077.1
supervision__CH0_PHASE_REARM_SAFE_G6: U51075.4, U51076.1
supervision__CH0_QUIET_DIS: D50410.1, R50420.1
supervision__CH0_QUIET_HI_OK: U50410.1, U51009.1
supervision__CH0_QUIET_LO_OK: U50410.7, U51009.3
supervision__CH0_QUIET_RAW: R50410.1, R50420.2, U51009.4
supervision__CH0_QUIET_RC: C50420.1, D50410.2, R50410.2, U50420.2
supervision__CH0_REQUEST_N: U51055.4, U51061.1, U51072.2, U51076.3
supervision__CH0_RUN_N: U51056.4, U51061.3, U51076.6
supervision__CH0_SEC_DIV: R58001.2, R58002.1, U50800.4
supervision__CH0_SEC_N: U50810.1, U51042.4
supervision__CH0_SEC_SET: R58000.1, U50800.3
supervision__CH0_SEC_TIMER: U50800.6, U51042.2, U51057.2, U51072.1, U51081.6
supervision__CH0_SEC_TIMER_N: U51057.4, U51061.6, U51077.2
supervision__CH0_STOP_N: U51073.4, U51074.2
supervision__CH0_TIMEOUT: U50810.5, U51043.1, U51068.2
supervision__CH0_TIMEOUT_D: U50810.2, U51043.4
supervision__CH1_ALLOW: J50005.11, U51095.4, U51097.2
supervision__CH1_ALLOW_G4: U51094.4, U51095.1
supervision__CH1_ALLOW_G6: U51093.4, U51094.1
supervision__CH1_BLOCK: U50911.5, U51092.2
supervision__CH1_BLOCK_CLR_N: U50911.6, U51091.4
supervision__CH1_BLOCK_PRE_N: U50911.7, U51087.4
supervision__CH1_DIFF_N: R50522.2, R50523.2, U50502.6
supervision__CH1_DIFF_P: R50520.2, R50521.2, U50502.5
supervision__CH1_ENDED: U51085.4, U51086.2
supervision__CH1_NO_BLOCK: U51092.4, U51093.3
supervision__CH1_NO_TIMEOUT: U51069.4, U51070.6, U51093.6, U51096.6
supervision__CH1_PAIR_HI_OK: U50520.1, U51012.1
supervision__CH1_PAIR_LO_OK: U50520.7, U51012.2
supervision__CH1_PAIR_OK: U51012.4, U51051.2
supervision__CH1_PHASE_HEALTH: U51084.4, U51087.1, U51088.3, U51093.1
supervision__CH1_PHASE_REARM_SAFE: U51090.4, U51091.2
supervision__CH1_PHASE_REARM_SAFE_G4: U51089.4, U51090.1
supervision__CH1_PHASE_REARM_SAFE_G6: U51088.4, U51089.1
supervision__CH1_QUIET_DIS: D50411.1, R50421.1
supervision__CH1_QUIET_HI_OK: U50411.1, U51010.1
supervision__CH1_QUIET_LO_OK: U50411.7, U51010.3
supervision__CH1_QUIET_RAW: R50411.1, R50421.2, U51010.4
supervision__CH1_QUIET_RC: C50421.1, D50411.2, R50411.2, U50421.2
supervision__CH1_REQUEST_N: U51058.4, U51062.3, U51085.2, U51089.3
supervision__CH1_RUN_N: U51059.4, U51062.6, U51089.6
supervision__CH1_SEC_DIV: R58011.2, R58012.1, U50801.4
supervision__CH1_SEC_N: U50811.1, U51044.4
supervision__CH1_SEC_SET: R58010.1, U50801.3
supervision__CH1_SEC_TIMER: U50801.6, U51044.2, U51060.2, U51085.1, U51094.6
supervision__CH1_SEC_TIMER_N: U51060.4, U51063.2, U51090.2
supervision__CH1_STOP_N: U51086.4, U51087.2
supervision__CH1_TIMEOUT: U50811.5, U51045.1, U51069.2
supervision__CH1_TIMEOUT_D: U50811.2, U51045.4
supervision__H3_OV: R52022.2, R52023.1, U50202.4
supervision__H3_RAIL_OK: R52024.2, U50202.1, U50202.6, U51000.6
supervision__H3_UV: R52020.2, R52021.1, U50202.3
supervision__H5_OV: R52032.2, R52033.1, U50203.4
supervision__H5_RAIL_OK: R52034.2, U50203.1, U50203.6, U51001.3
supervision__H5_UV: R52030.2, R52031.1, U50203.3
supervision__H15_OV: R52042.2, R52043.1, U50204.4
supervision__H15_RAIL_OK: R52044.2, U50204.1, U50204.6, U51001.6
supervision__H15_UV: R52040.2, R52041.1, U50204.3
supervision__H24_OV: R52052.2, R52053.1, U50205.4
supervision__H24_RAIL_OK: R52054.2, U50205.1, U50205.6, U51002.3
supervision__H24_UV: R52050.2, R52051.1, U50205.3
supervision__HOST_RAILS_OK: U50300.3, U51002.4, U51006.2, U51007.6, U51046.1, U51047.1, U51049.1
supervision__HOST_RAILS_OK_G5: U51001.4, U51002.1
supervision__HOST_RAILS_OK_G7: U51000.4, U51001.1
supervision__NO_ACTIVITY: U51063.4, U51065.2
supervision__NO_ACTIVITY_G4: U51062.4, U51063.1
supervision__NO_ACTIVITY_G6: U51061.4, U51062.1
supervision__PAIR_HI: U50500.3, U50500.4, U50510.3, U50520.3
supervision__PAIR_HI_DIV: R50500.2, R50501.1, U50500.1
supervision__PAIR_LO: U50501.3, U50501.4, U50510.6, U50520.6
supervision__PAIR_LO_DIV: R50501.2, R50502.1, U50501.1
supervision__QUIET_HI: U50400.3, U50400.4, U50410.3, U50411.3
supervision__QUIET_HI_DIV: R50400.2, R50401.1, U50400.1
supervision__QUIET_LO: U50401.3, U50401.4, U50410.6, U50411.6
supervision__QUIET_LO_DIV: R50401.2, R50402.1, U50401.1
supervision__RAW_HEALTH: U51054.4, U51064.1, U51070.1, U51071.1, U51083.1, U51084.1, U51096.1
supervision__REC00_DC_OK: U51013.4, U51032.1
supervision__REC00_HI_OK: U50600.1, U51013.1
supervision__REC00_LO_OK: U50600.7, U51013.2
supervision__REC00_SENSE: R56000.2, R56001.2, U50600.2, U50600.5
supervision__REC01_DC_OK: U51014.4, U51032.3
supervision__REC01_HI_OK: U50601.1, U51014.1
supervision__REC01_LO_OK: U50601.7, U51014.2
supervision__REC01_SENSE: R56010.2, R56011.2, U50601.2, U50601.5
supervision__REC02_DC_OK: U51015.4, U51032.6
supervision__REC02_HI_OK: U50602.1, U51015.1
supervision__REC02_LO_OK: U50602.7, U51015.2
supervision__REC02_SENSE: R56020.2, R56021.2, U50602.2, U50602.5
supervision__REC03_DC_OK: U51016.4, U51033.3
supervision__REC03_HI_OK: U50603.1, U51016.1
supervision__REC03_LO_OK: U50603.7, U51016.2
supervision__REC03_SENSE: R56030.2, R56031.2, U50603.2, U50603.5
supervision__REC04_DC_OK: U51017.4, U51033.6
supervision__REC04_HI_OK: U50604.1, U51017.1
supervision__REC04_LO_OK: U50604.7, U51017.2
supervision__REC04_SENSE: R56040.2, R56041.2, U50604.2, U50604.5
supervision__REC05_DC_OK: U51018.4, U51034.3
supervision__REC05_HI_OK: U50605.1, U51018.1
supervision__REC05_LO_OK: U50605.7, U51018.2
supervision__REC05_SENSE: R56050.2, R56051.2, U50605.2, U50605.5
supervision__REC06_DC_OK: U51019.4, U51034.6
supervision__REC06_HI_OK: U50606.1, U51019.1
supervision__REC06_LO_OK: U50606.7, U51019.2
supervision__REC06_SENSE: R56060.2, R56061.2, U50606.2, U50606.5
supervision__REC07_DC_OK: U51020.4, U51035.3
supervision__REC07_HI_OK: U50607.1, U51020.1
supervision__REC07_LO_OK: U50607.7, U51020.2
supervision__REC07_SENSE: R56070.2, R56071.2, U50607.2, U50607.5
supervision__REC08_DC_OK: U51021.4, U51035.6
supervision__REC08_HI_OK: U50608.1, U51021.1
supervision__REC08_LO_OK: U50608.7, U51021.2
supervision__REC08_SENSE: R56080.2, R56081.2, U50608.2, U50608.5
supervision__REC09_DC_OK: U51022.4, U51036.3
supervision__REC09_HI_OK: U50609.1, U51022.1
supervision__REC09_LO_OK: U50609.7, U51022.2
supervision__REC09_SENSE: R56090.2, R56091.2, U50609.2, U50609.5
supervision__REC10_DC_OK: U51023.4, U51036.6
supervision__REC10_HI_OK: U50610.1, U51023.1
supervision__REC10_LO_OK: U50610.7, U51023.2
supervision__REC10_SENSE: R56100.2, R56101.2, U50610.2, U50610.5
supervision__REC11_DC_OK: U51024.4, U51037.3
supervision__REC11_HI_OK: U50611.1, U51024.1
supervision__REC11_LO_OK: U50611.7, U51024.2
supervision__REC11_SENSE: R56110.2, R56111.2, U50611.2, U50611.5
supervision__REC12_DC_OK: U51025.4, U51037.6
supervision__REC12_HI_OK: U50612.1, U51025.1
supervision__REC12_LO_OK: U50612.7, U51025.2
supervision__REC12_SENSE: R56120.2, R56121.2, U50612.2, U50612.5
supervision__REC13_DC_OK: U51026.4, U51038.3
supervision__REC13_HI_OK: U50613.1, U51026.1
supervision__REC13_LO_OK: U50613.7, U51026.2
supervision__REC13_SENSE: R56130.2, R56131.2, U50613.2, U50613.5
supervision__REC14_DC_OK: U51027.4, U51038.6
supervision__REC14_HI_OK: U50614.1, U51027.1
supervision__REC14_LO_OK: U50614.7, U51027.2
supervision__REC14_SENSE: R56140.2, R56141.2, U50614.2, U50614.5
supervision__REC15_DC_OK: U51028.4, U51039.3
supervision__REC15_HI_OK: U50615.1, U51028.1
supervision__REC15_LO_OK: U50615.7, U51028.2
supervision__REC15_SENSE: R56150.2, R56151.2, U50615.2, U50615.5
supervision__REF_DC_OK: U51029.4, U51039.6
supervision__REF_HI_OK: U50616.1, U51029.1
supervision__REF_LO_OK: U50616.7, U51029.2
supervision__REF_SENSE: R56160.2, R56161.2, U50616.2, U50616.5
supervision__SAFE_IDLE: U50900.2, U51065.4, U51066.2
supervision__SAFE_IDLE_G4: U51064.4, U51065.1
supervision__SENSE_HEALTH: U51051.4, U51052.1, U51053.1, U51054.1
supervision__SENSE_HEALTH_G4: U51050.4, U51051.1
supervision__SENSE_HEALTH_G6: U51049.4, U51050.1
supervision__SUP3_OV: R52002.2, R52003.1, U50200.4
supervision__SUP3_RAIL_OK: R52004.2, U50200.1, U50200.6, U51000.1
supervision__SUP3_UV: R52000.2, R52001.1, U50200.3
supervision__SUP5_OV: R52012.2, R52013.1, U50201.4
supervision__SUP5_RAIL_OK: R52014.2, U50201.1, U50201.6, U51000.3
supervision__SUP5_UV: R52010.2, R52011.1, U50201.3
supervision__SUP_DIS: D50250.1, R50251.1
supervision__SUP_RC: C50250.1, D50250.2, R50250.2, U50250.2
supervision__SUP_STARTUP_OK: U50250.4, U51002.6
supervision__TIMEOUT_CLR_N: U50810.6, U50811.6, U51067.4
supervision__TIMEOUT_RESET: U51066.4, U51067.2
supervision__WDI_N: U50301.1, U51005.4
supervision__WD_CWD: R50300.2, U50300.2
supervision__WD_ENOUT_OK: R50301.2, U50300.7, U50300.8, U50301.2, U51006.1, U51007.1
supervision__WD_GOOD: U51007.4, U51008.1, U51047.6, U51049.6
supervision__WD_SEEN: U50301.5, U51007.3
supervision__WD_SEEN_CLR_N: U50301.6, U51006.4
